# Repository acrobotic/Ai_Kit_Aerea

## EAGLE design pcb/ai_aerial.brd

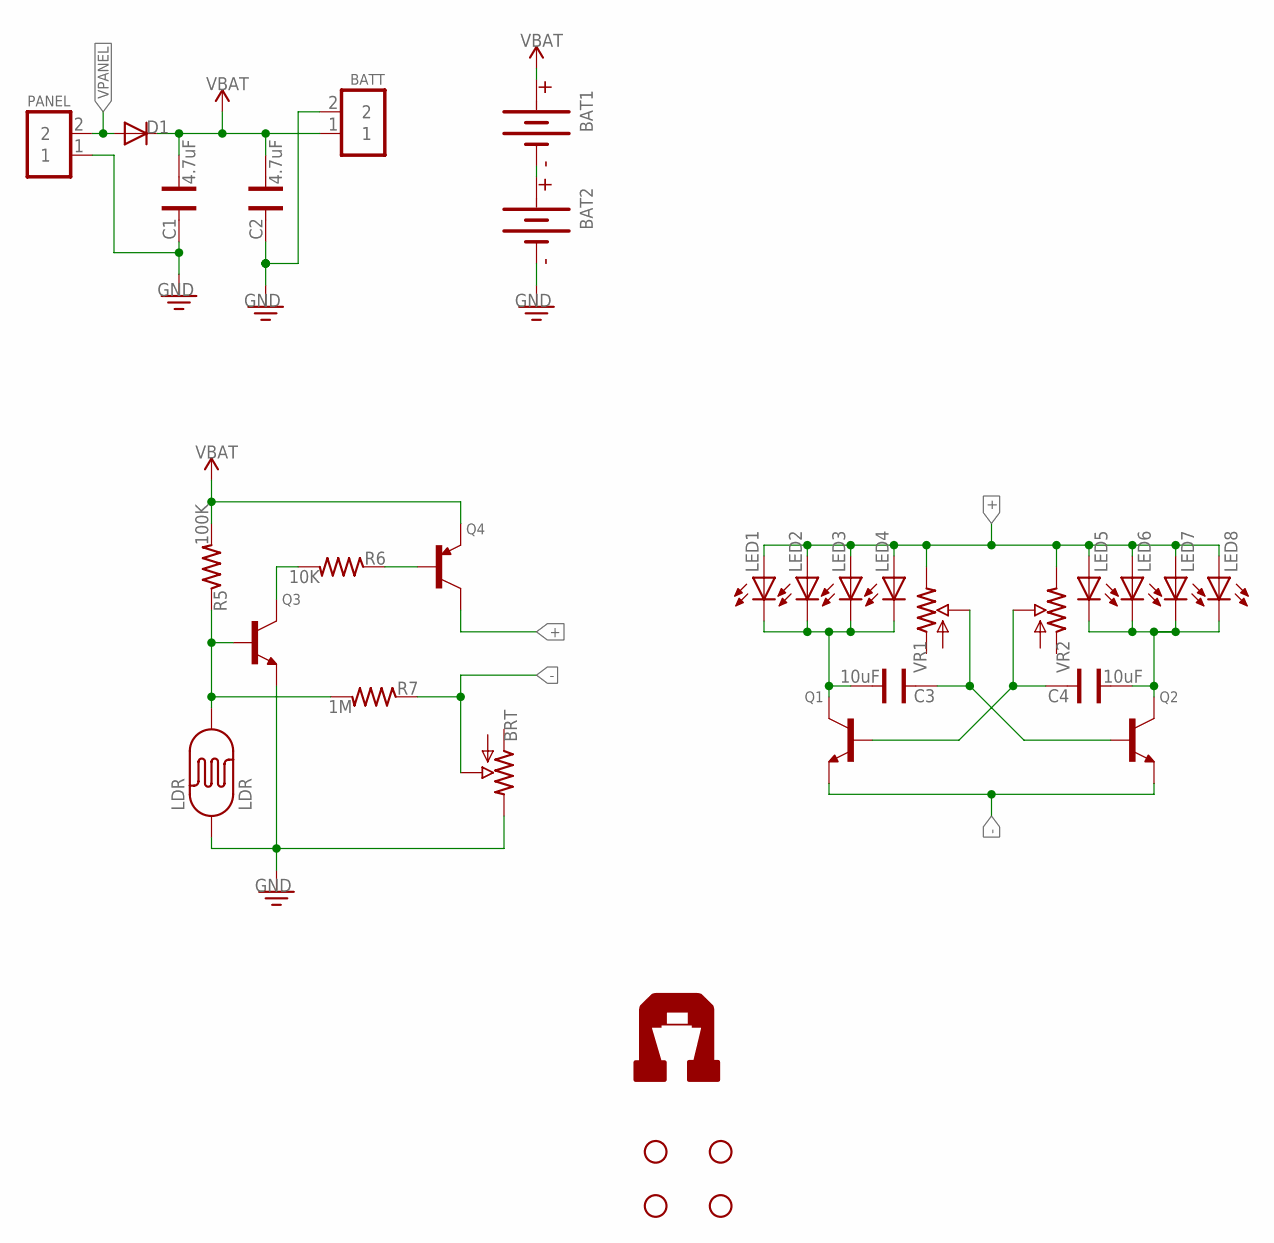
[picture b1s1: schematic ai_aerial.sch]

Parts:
BAT1, BAT2: BATTERY-HOLDER; BATTERY-AAA
BATT: 1X02ST; 1X02-ST
BRT: POT05X05; POT-05X05
C1, C2: 4.7uF; CAP-025X050
C3, C4: 10uF; CAP-025X050
D1: DIODETH-1N914; TH-1N914
LDR: LDR-PTH; LDR
LED1, LED2, LED3, LED4, LED5, LED6, LED7, LED8: LED5MM; LED-5MM
PANEL: 1X02ST; 1X02-ST
Q1, Q2, Q3: TRANSISTOR-NPN; TO-92-NPN
Q4: TRANSISTOR-PNP; TO-92-PNP
R5: 100K; RES-AXIAL-0.4
R6: 10K; RES-AXIAL-0.4
R7: 1M; RES-AXIAL-0.4
STANDOFF1, STANDOFF2, STANDOFF3, STANDOFF4: STAND-OFF
U$4: AI-LOGOM; AI-LOGO-M
VR1, VR2: POT05X05; POT-05X05

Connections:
+: LED1.A, LED2.A, LED3.A, LED4.A, LED5.A, LED6.A, LED7.A, LED8.A, Q4.1 (C), VR1.1 (E), VR2.1 (E)
-: BRT.2 (S), Q1.1 (E), Q2.1 (E), R7.P$1 (1)
GND: BAT2.GND@1 (-), BAT2.GND@2 (-), BATT.2, BRT.1 (E), C1.2, C2.2, LDR.1, PANEL.1, Q3.1 (E)
unnamed: BAT1.GND@1 (-), BAT1.GND@2 (-), BAT2.PWR@1 (+), BAT2.PWR@2 (+)
unnamed: C4.1, LED5.C, LED6.C, LED7.C, LED8.C, Q2.3 (C)
unnamed: C3.2, Q2.2 (B), VR1.2 (S)
unnamed: C4.2, Q1.2 (B), VR2.2 (S)
unnamed: LDR.2, Q3.2 (B), R5.P$1 (1), R7.P$2 (2)
unnamed: Q3.3 (C), R6.P$2 (2)
unnamed: Q4.2 (B), R6.P$1 (1)
unnamed: C3.1, LED1.C, LED2.C, LED3.C, LED4.C, Q1.3 (C)
VBAT: BAT1.PWR@1 (+), BAT1.PWR@2 (+), BATT.1, C1.1, C2.1, D1.C, Q4.3 (E), R5.P$2 (2)
VPANEL: D1.A, PANEL.2

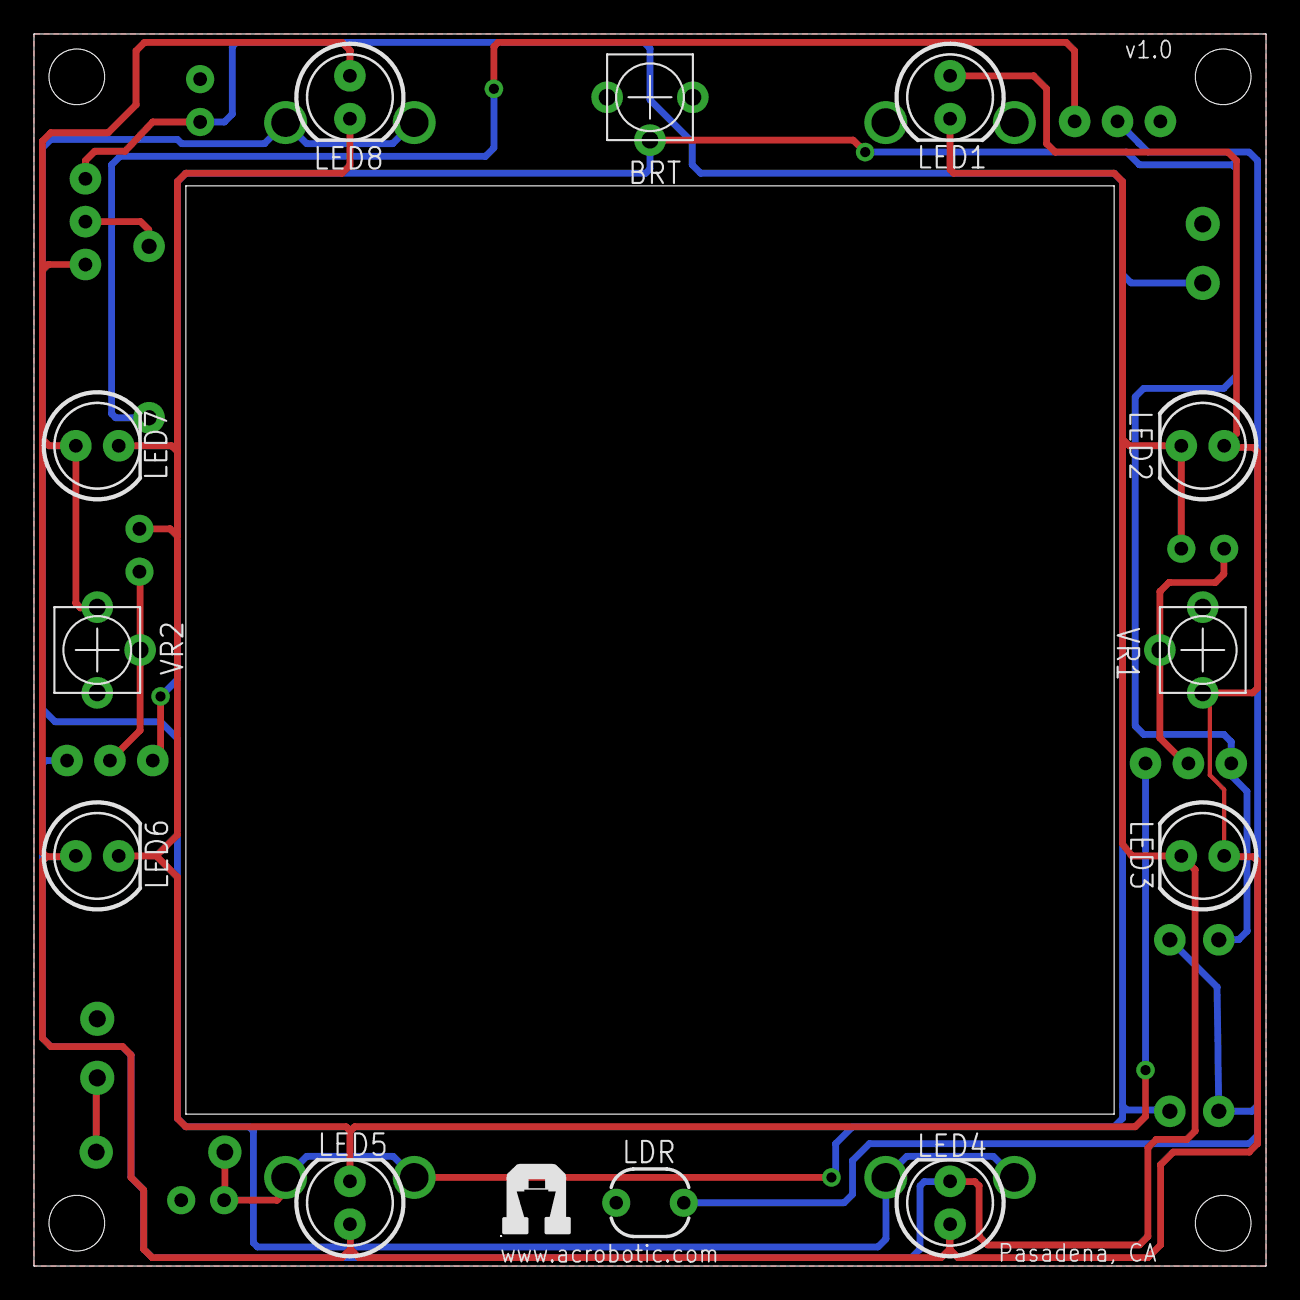
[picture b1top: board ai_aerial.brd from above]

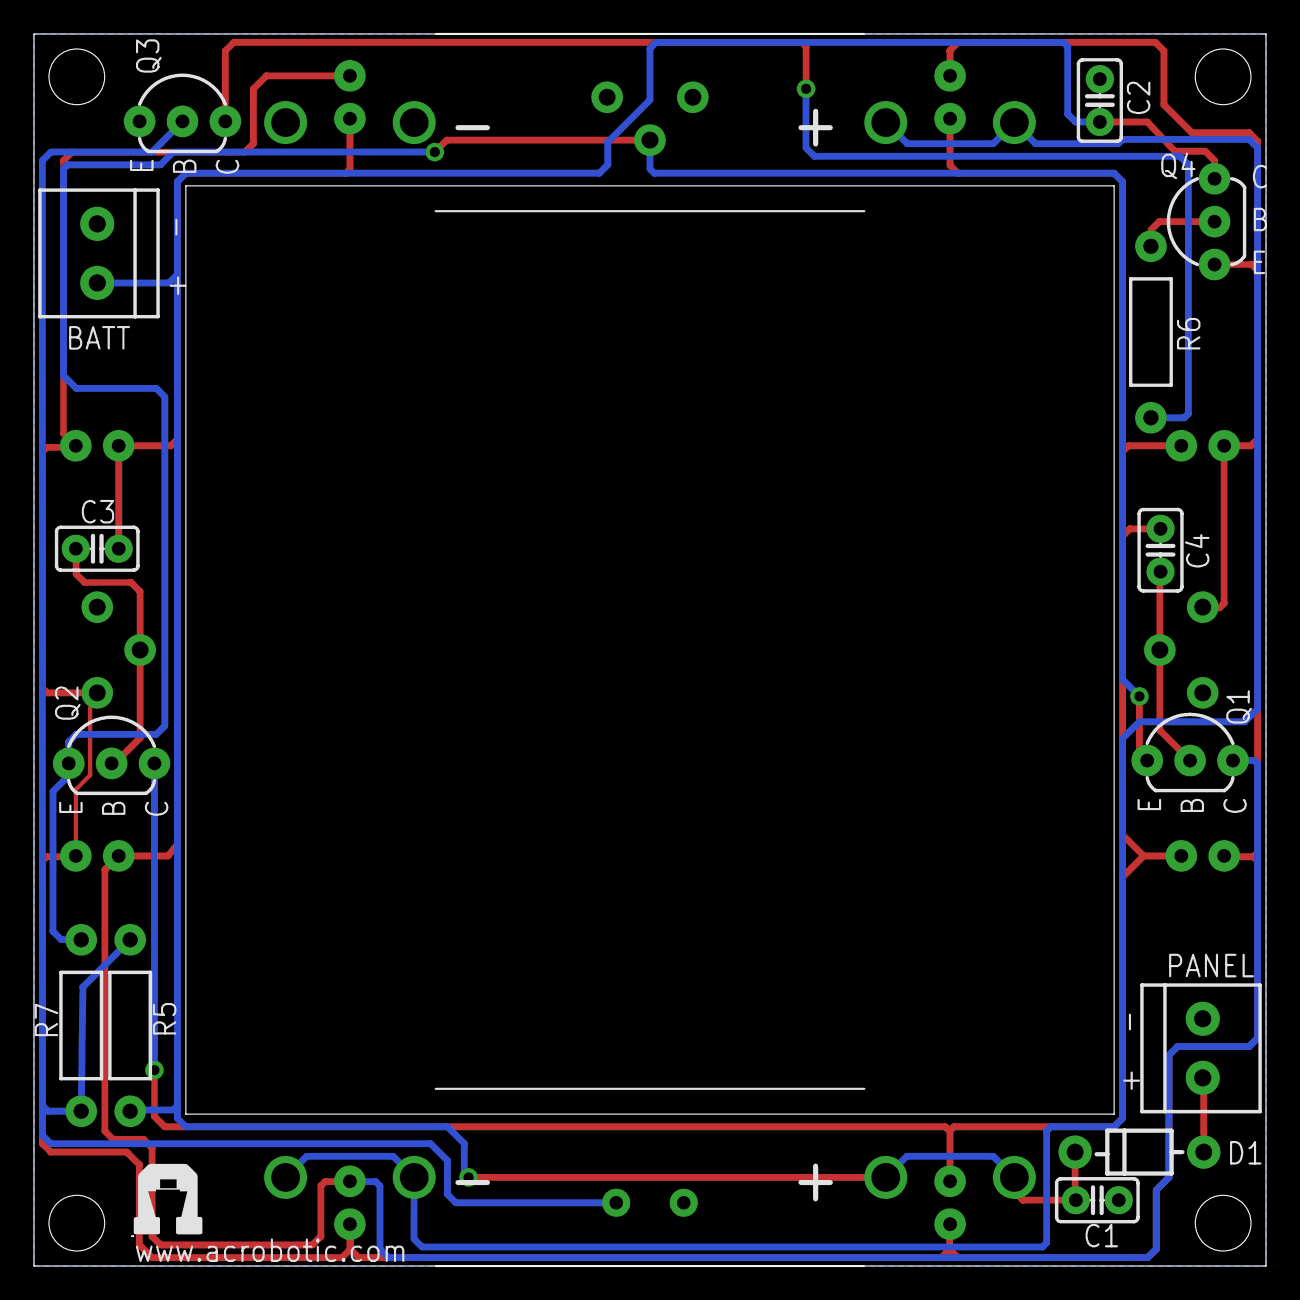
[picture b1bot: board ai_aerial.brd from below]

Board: 2 copper layers, 73.0 x 73.0 mm, 34 parts (17 on the bottom side), 13 nets.

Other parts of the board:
U$3: AI-LOGOM; AI-LOGO-M

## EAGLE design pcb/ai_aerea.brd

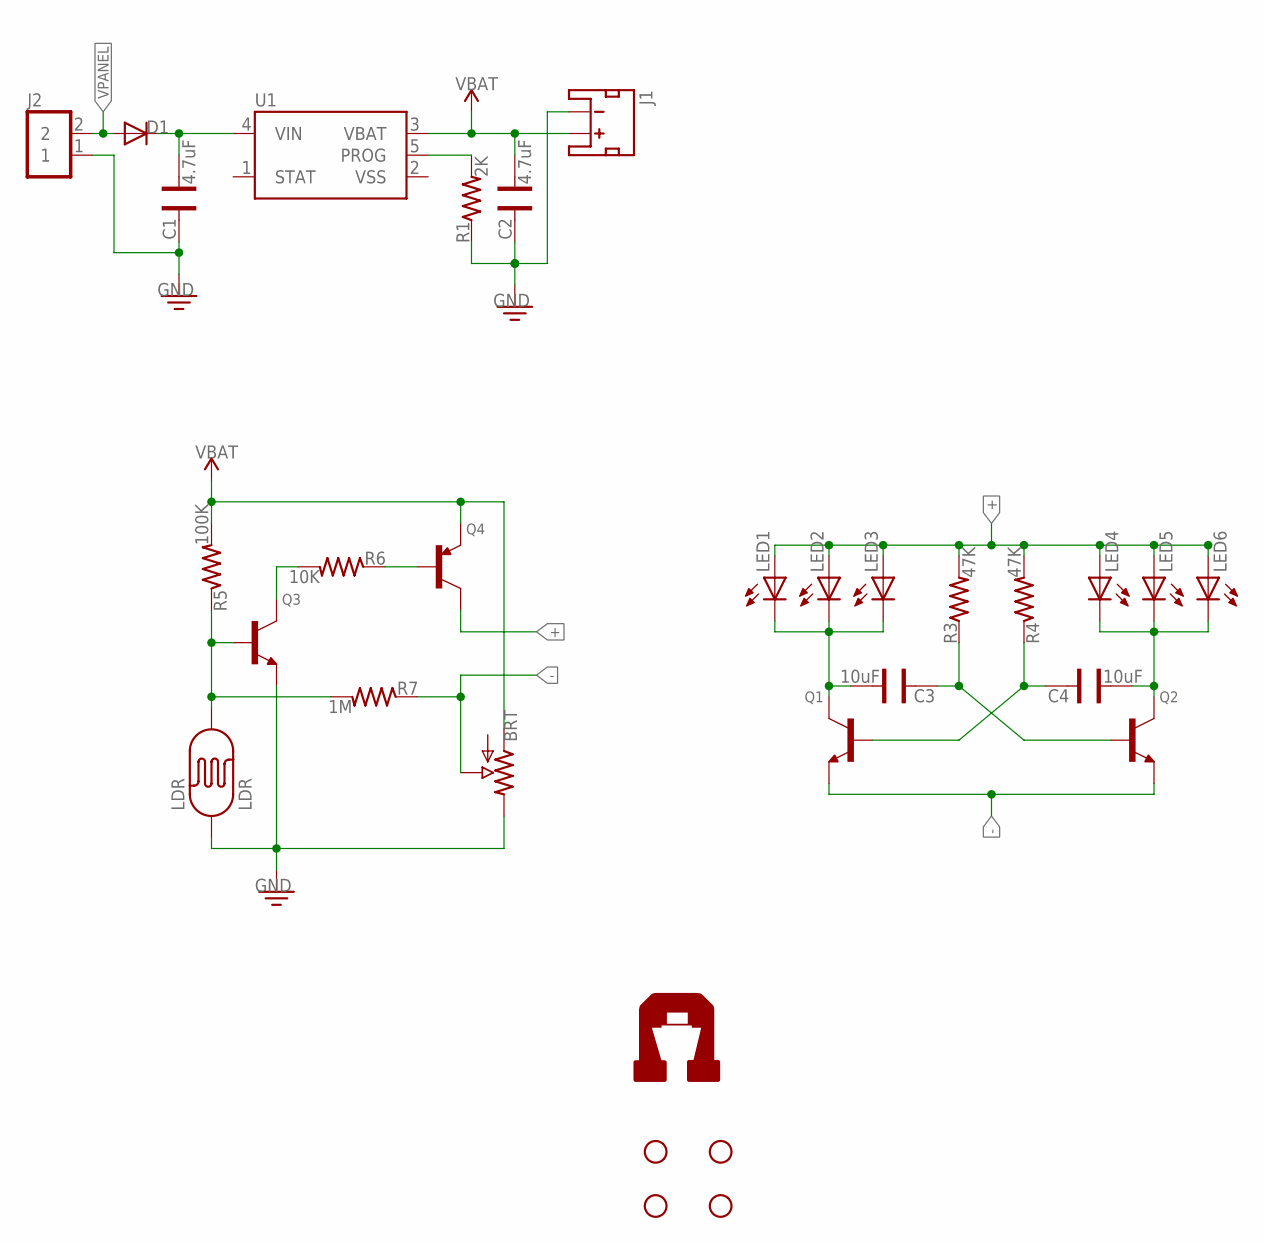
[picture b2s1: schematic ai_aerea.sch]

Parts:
BRT: POT05X05; POT-05X05
C1, C2: 4.7uF; CAP-025X050
C3, C4: 10uF; CAP-025X050
D1: DIODETH-1N914; TH-1N914
J1: JST-2-MALE; JST-2-SMD
J2: 1X02ST; 1X02-ST
LDR: LDR-PTH; LDR
LED1, LED2, LED3, LED4, LED5, LED6: LED5MM; LED-5MM
Q1, Q2, Q3: TRANSISTOR-NPN; TO-92-NPN
Q4: TRANSISTOR-PNP; TO-92-PNP
R1: 2K; RES-AXIAL-0.4
R3, R4: 47K; RES-AXIAL-0.4
R5: 100K; RES-AXIAL-0.4
R6: 10K; RES-AXIAL-0.4
R7: 1M; RES-AXIAL-0.4
STANDOFF1, STANDOFF2, STANDOFF3, STANDOFF4: STAND-OFF
U1: MCP73831; SOT23-5
U$4: AI-LOGOM; AI-LOGO-M

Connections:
+: LED1.A, LED2.A, LED3.A, LED4.A, LED5.A, LED6.A, Q4.1 (C), R3.P$2 (2), R4.P$2 (2)
-: BRT.2 (S), Q1.1 (E), Q2.1 (E), R7.P$1 (1)
GND: BRT.1 (E), C1.2, C2.2, J1.2 (-), J2.1, LDR.1, Q3.1 (E), R1.P$1 (1)
unnamed: C1.1, D1.C, U1.4 (VIN)
unnamed: R1.P$2 (2), U1.5 (PROG)
unnamed: C3.2, Q2.2 (B), R3.P$1 (1)
unnamed: C4.2, Q1.2 (B), R4.P$1 (1)
unnamed: C4.1, LED4.C, LED5.C, LED6.C, Q2.3 (C)
unnamed: LDR.2, Q3.2 (B), R5.P$1 (1), R7.P$2 (2)
unnamed: Q3.3 (C), R6.P$2 (2)
unnamed: Q4.2 (B), R6.P$1 (1)
unnamed: C3.1, LED1.C, LED2.C, LED3.C, Q1.3 (C)
VBAT: BRT.3 (A), C2.1, J1.1 (+), Q4.3 (E), R5.P$2 (2), U1.3 (VBAT)
VPANEL: D1.A, J2.2
VSS: U1.2 (VSS)

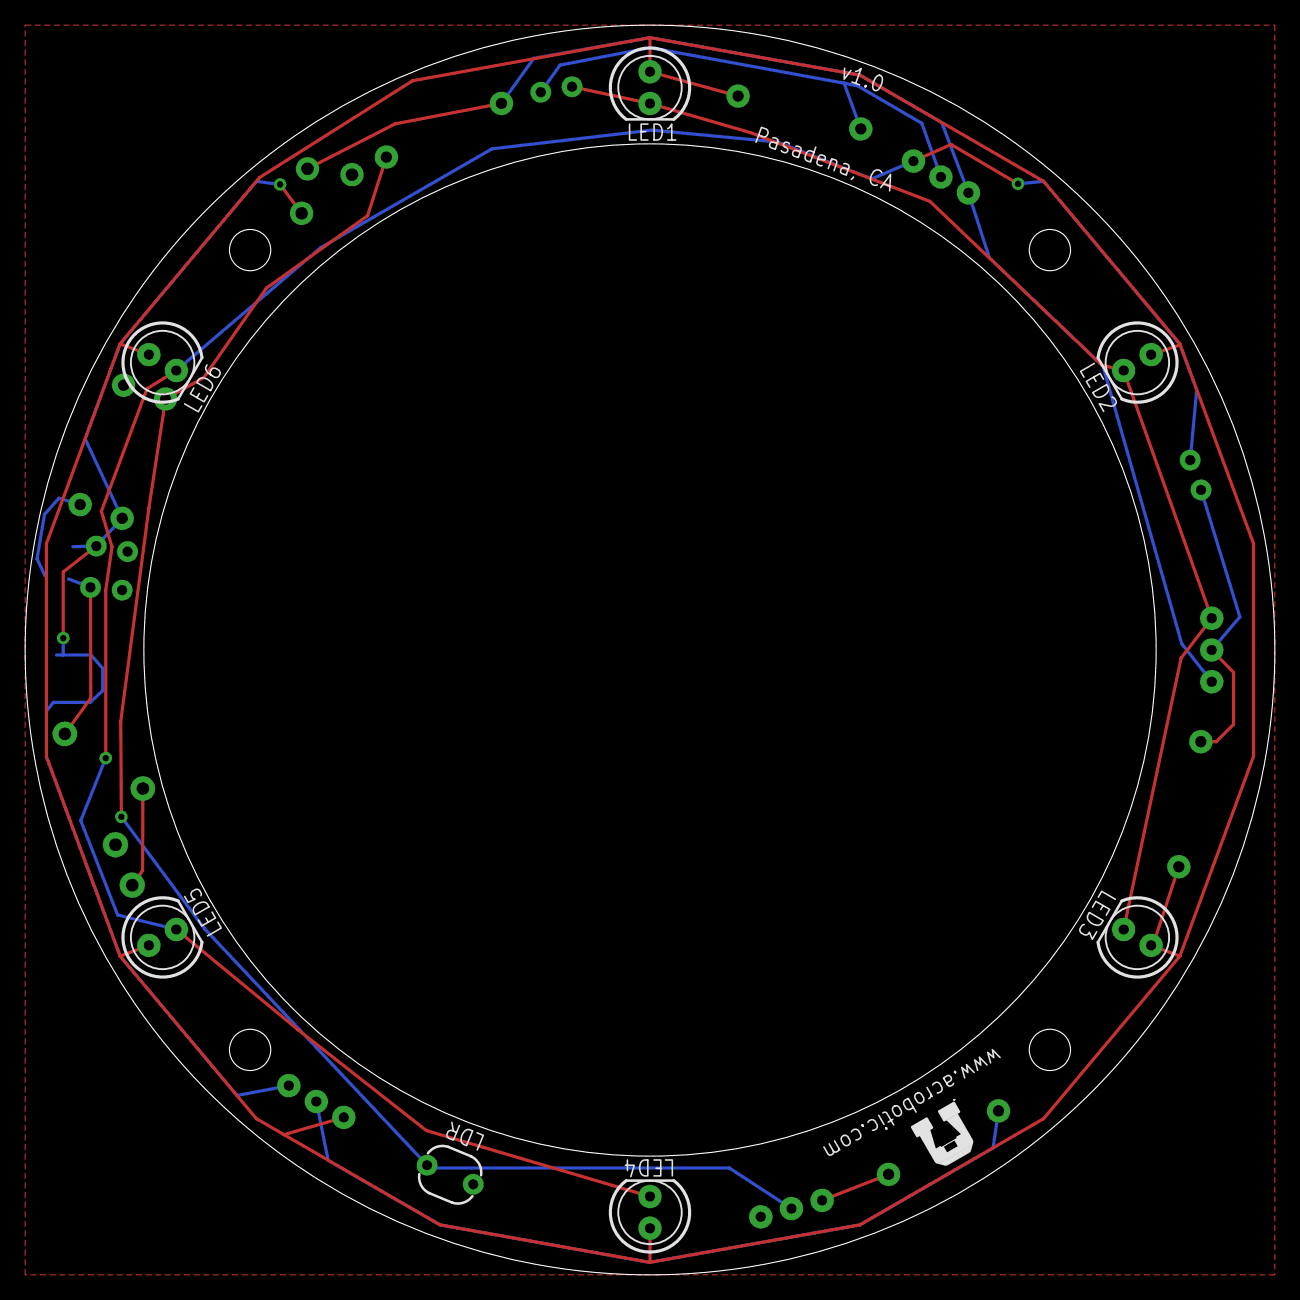
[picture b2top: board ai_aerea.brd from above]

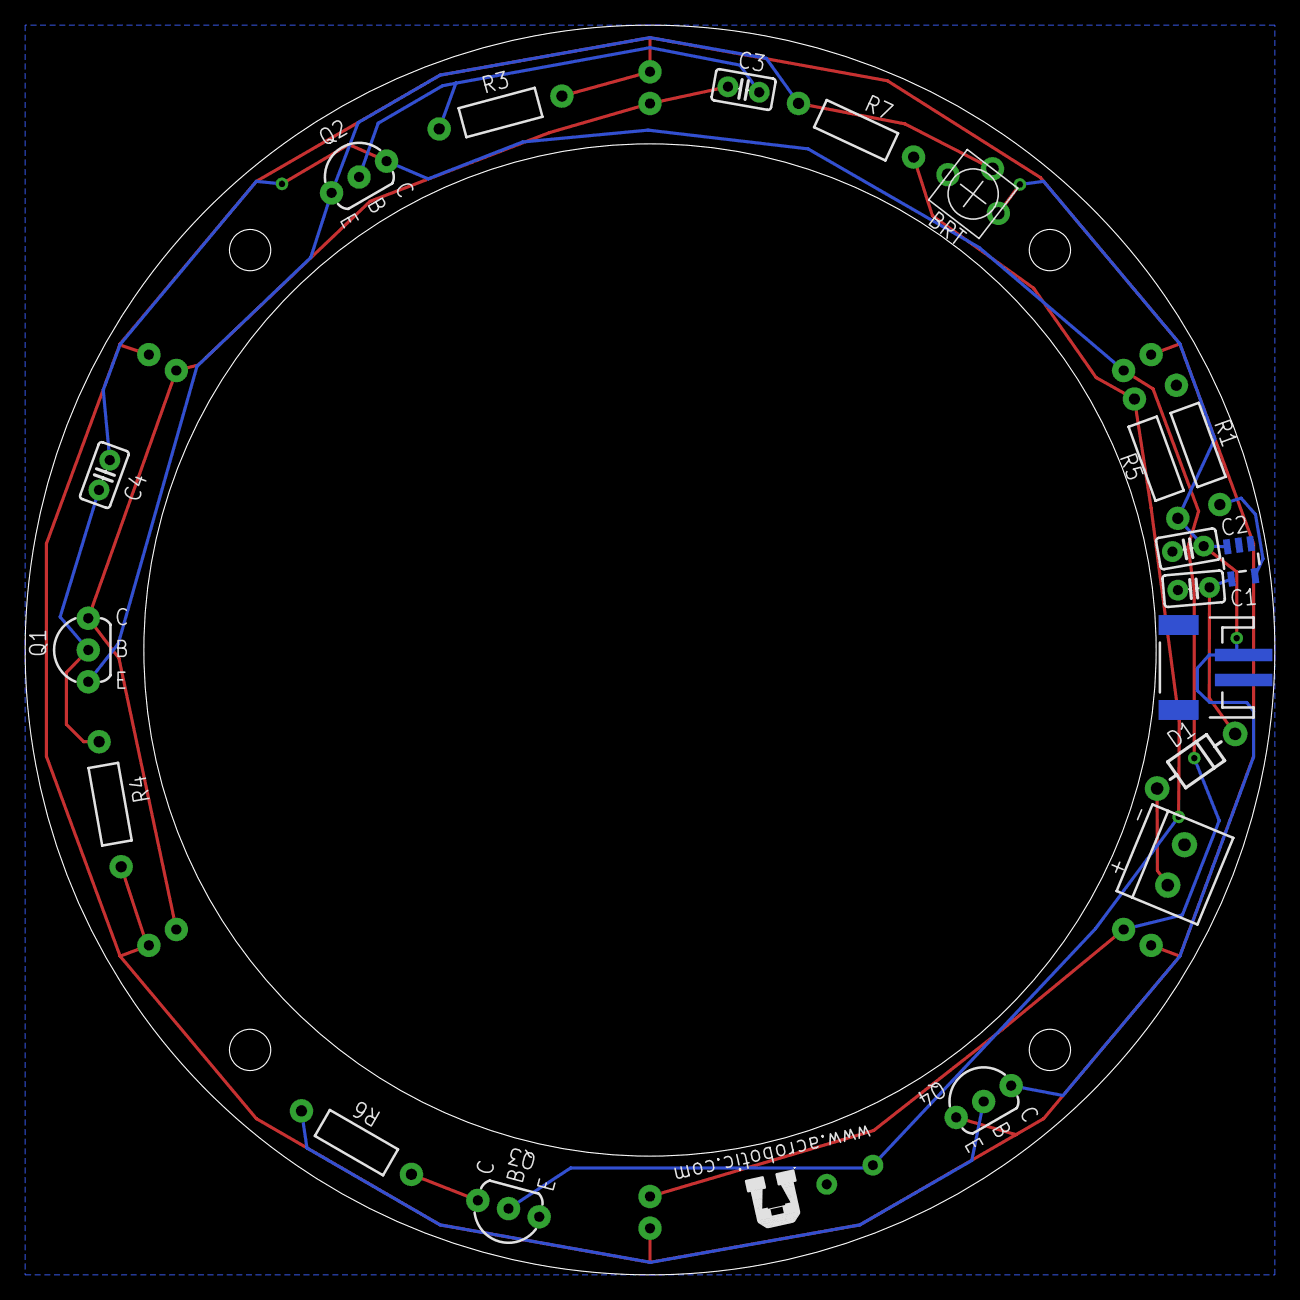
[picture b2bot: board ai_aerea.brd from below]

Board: 2 copper layers, 100.0 x 100.0 mm, 32 parts (20 on the bottom side), 14 nets.

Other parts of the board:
U$3: AI-LOGOM; AI-LOGO-M

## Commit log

2014-10-04 routing
2014-10-04 routed
2014-10-04 gerbers generated
2014-10-12 going with a square design
2014-10-17 renaming
2014-10-20 updating libs
2014-10-26 fixing trace error
